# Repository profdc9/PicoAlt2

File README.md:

# Pico Alt 2

This is a simplified Pi Pico board for the new RP2350.  This has been fabricated by JLCPCB and a photograph of the result is below.  It is tested to download sketches. I customized it to add more flash (16 MB), a linear regulator (AMS1117-3.3), and to be easier to modify if needed.

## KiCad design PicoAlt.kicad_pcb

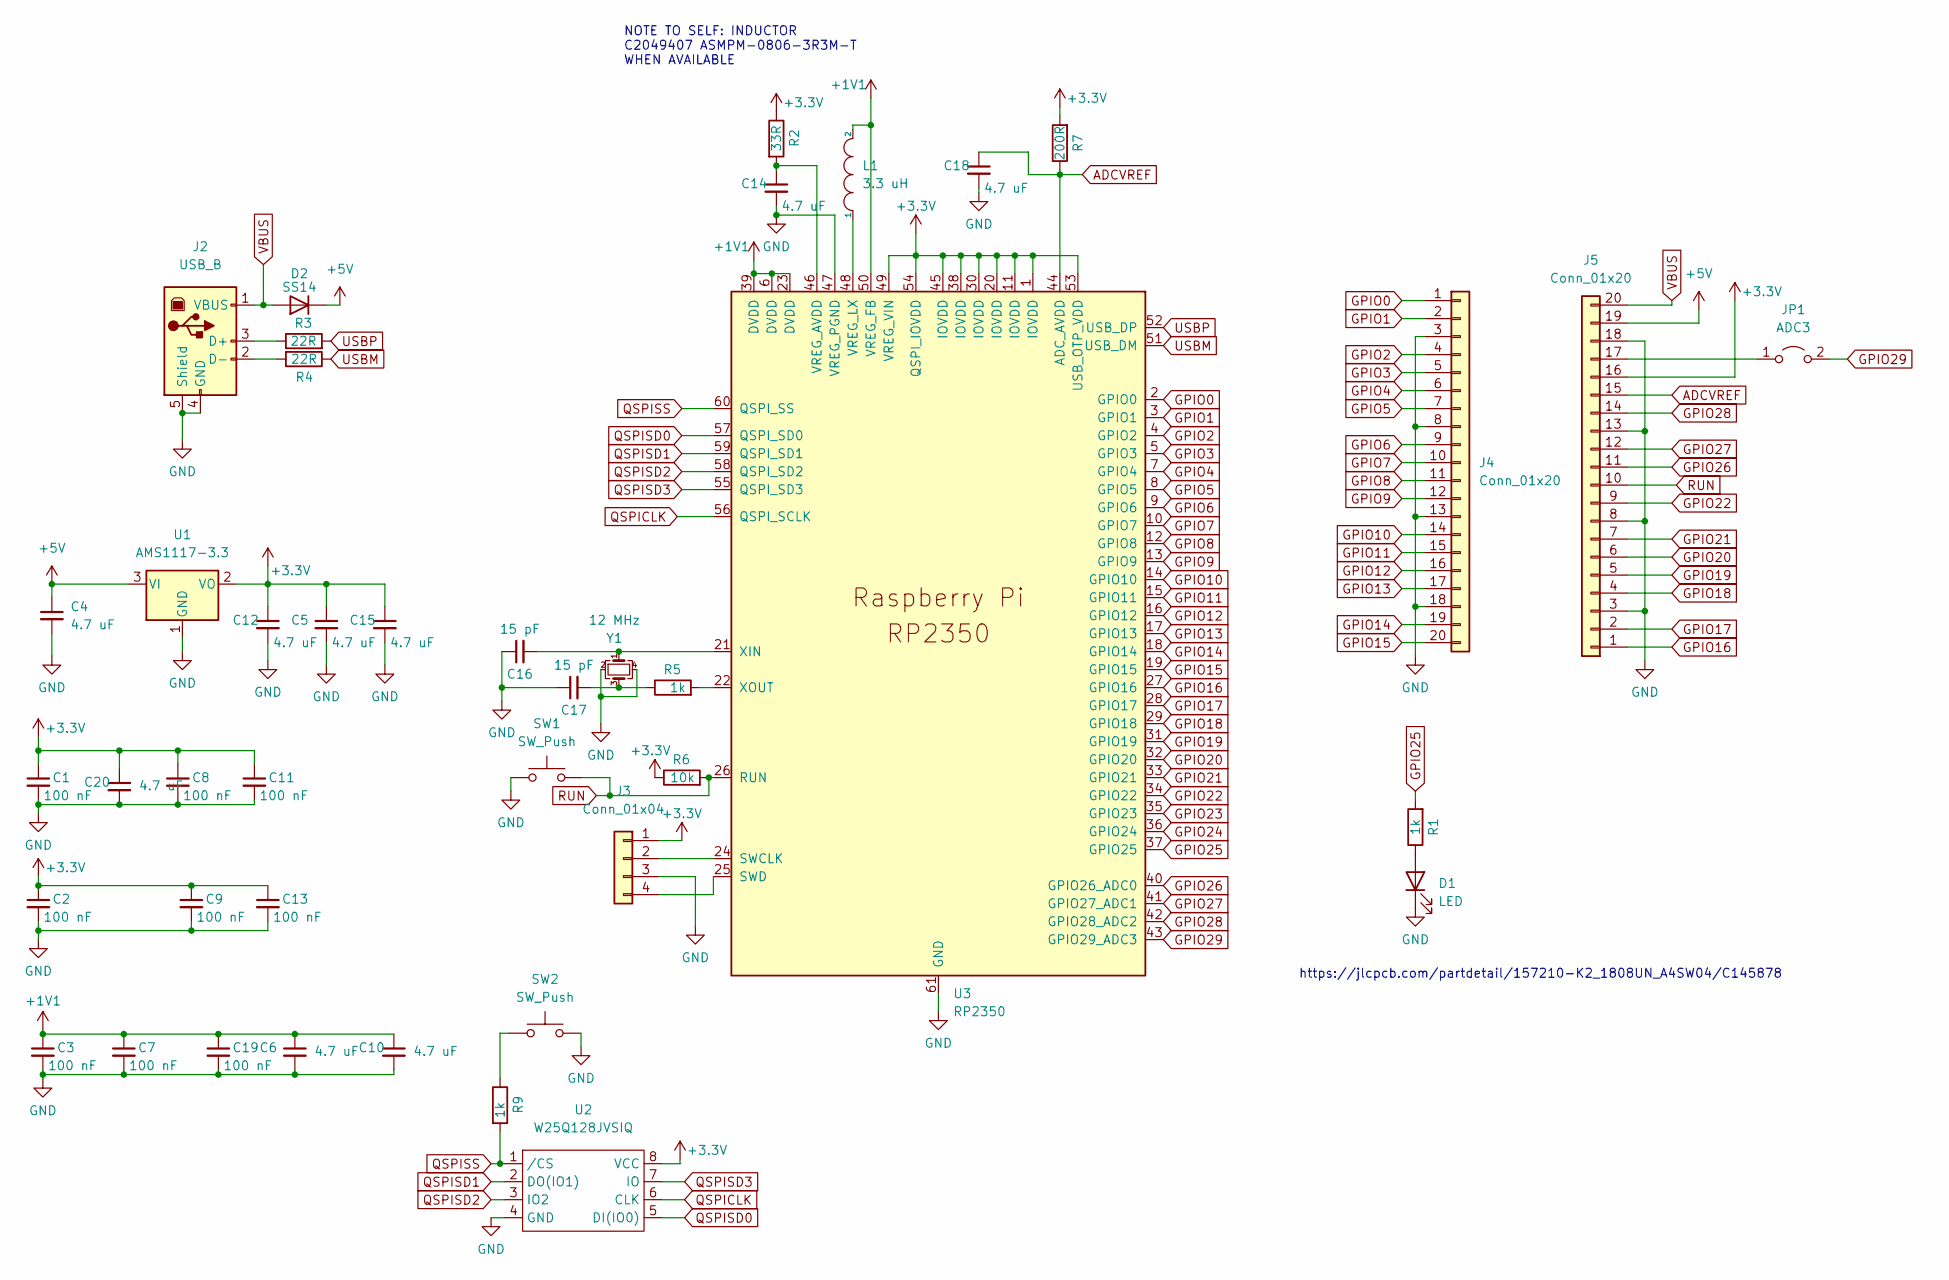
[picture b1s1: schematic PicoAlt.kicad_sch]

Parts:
C1, C2, C3, C7, C8, C9, C11, C13, C19: 100 nF; C_0402_1005Metric; LCSC C307331
C4, C5, C6, C10, C12, C14, C15, C18, C20: 4.7 uF; C_0603_1608Metric; LCSC C19666
C16, C17: 15 pF; C_0402_1005Metric; LCSC C1548
D1: LED; LED_0603_1608Metric_Pad1.05x0.95mm_HandSolder; LCSC C2286
D2: SS14; D_SMA; LCSC C2480
J2: USB_B; USB_B_OST_USB-B1HSxx_Horizontal
J3: Conn_01x04; PinHeader_1x04_P2.54mm_Vertical
J4, J5: Conn_01x20; PinHeader_1x20_P2.54mm_Vertical
JP1: ADC3; PinHeader_1x02_P2.54mm_Vertical
L1: 3.3 uH; Abracon_Pico_inductor; LCSC C42411119
R1: 1k; R_0603_1608Metric_Pad0.98x0.95mm_HandSolder; LCSC C21190
R2: 33R; R_0402_1005Metric; LCSC C25105
R3, R4: 22R; R_0402_1005Metric; LCSC C25092
R5, R9: 1k; R_0402_1005Metric; LCSC C11702
R6: 10k; R_0603_1608Metric; LCSC C25804
R7: 200R; R_0603_1608Metric_Pad0.98x0.95mm_HandSolder; LCSC C22962
SW1, SW2: SW_Push; K2-1808UN; LCSC C145878
U1: AMS1117-3.3; SOT-223-3_TabPin2; LCSC C6186
U2: W25Q128JVSIQ; SOIC-8_3.9x4.9mm_P1.27mm_mod; LCSC C97521
U3: RP2350; QFN-60-1EP_7x7mm_P0.4mm_EP3.2x3.2mm; LCSC C42411118
Y1: 12 MHz; Crystal_SMD_3225-4Pin_3.2x2.5mm; LCSC C20625731

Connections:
+1V1: C3.1, C6.1, C7.1, C10.1, C19.1, L1.2, U3.6 (DVDD), U3.23 (DVDD), U3.39 (DVDD), U3.50 (VREG_FB)
+3.3V: C1.1, C2.1, C5.1, C8.1, C9.1, C11.1, C12.1, C13.1, C15.1, C20.1, J3.1, J5.16, R2.1, R6.1, R7.2, U1.2 (VO), U2.8 (VCC), U3.1 (IOVDD), U3.11 (IOVDD), U3.20 (IOVDD), U3.30 (IOVDD), U3.38 (IOVDD), U3.45 (IOVDD), U3.49 (VREG_VIN), U3.53 (USB_OTP_VDD), U3.54 (QSPI_IOVDD)
+5V: C4.1, D2.1 (K), J5.19, U1.3 (VI)
ADCVREF: C18.1, J5.15, R7.1, U3.44 (ADC_AVDD)
GND: C1.2, C2.2, C3.2, C4.2, C5.2, C6.2, C7.2, C8.2, C9.2, C10.2, C11.2, C12.2, C13.2, C14.2, C15.2, C16.1, C17.1, C18.2, C19.2, C20.2, D1.1 (K), J2.4 (GND), J2.5 (Shield), J3.3, J4.3, J4.8, J4.13, J4.18, J5.3, J5.8, J5.13, J5.18, SW1.1, SW2.2, U1.1 (GND), U2.4 (GND), U3.47 (VREG_PGND), U3.61 (GND), Y1.2, Y1.4
GPIO0: J4.1, U3.2 (GPIO0)
GPIO1: J4.2, U3.3 (GPIO1)
GPIO2: J4.4, U3.4 (GPIO2)
GPIO3: J4.5, U3.5 (GPIO3)
GPIO4: J4.6, U3.7 (GPIO4)
GPIO5: J4.7, U3.8 (GPIO5)
GPIO6: J4.9, U3.9 (GPIO6)
GPIO7: J4.10, U3.10 (GPIO7)
GPIO8: J4.11, U3.12 (GPIO8)
GPIO9: J4.12, U3.13 (GPIO9)
GPIO10: J4.14, U3.14 (GPIO10)
GPIO11: J4.15, U3.15 (GPIO11)
GPIO12: J4.16, U3.16 (GPIO12)
GPIO13: J4.17, U3.17 (GPIO13)
GPIO14: J4.19, U3.18 (GPIO14)
GPIO15: J4.20, U3.19 (GPIO15)
GPIO16: J5.1, U3.27 (GPIO16)
GPIO17: J5.2, U3.28 (GPIO17)
GPIO18: J5.4, U3.29 (GPIO18)
GPIO19: J5.5, U3.31 (GPIO19)
GPIO20: J5.6, U3.32 (GPIO20)
GPIO21: J5.7, U3.33 (GPIO21)
GPIO22: J5.9, U3.34 (GPIO22)
GPIO23: U3.35 (GPIO23)
GPIO24: U3.36 (GPIO24)
GPIO25: R1.2, U3.37 (GPIO25)
GPIO26: J5.11, U3.40 (GPIO26_ADC0)
GPIO27: J5.12, U3.41 (GPIO27_ADC1)
GPIO28: J5.14, U3.42 (GPIO28_ADC2)
GPIO29: JP1.2 (B), U3.43 (GPIO29_ADC3)
unnamed: C17.2, R5.1, Y1.3
unnamed: D1.2 (A), R1.1
unnamed: J2.3 (D+), R3.1
unnamed: J2.2 (D-), R4.2
unnamed: J3.2, U3.24 (SWCLK)
unnamed: J3.4, U3.25 (SWD)
unnamed: J5.17, JP1.1 (A)
unnamed: R9.1, SW2.1
unnamed: C14.1, R2.2, U3.46 (VREG_AVDD)
unnamed: L1.1, U3.48 (VREG_LX)
unnamed: C16.2, U3.21 (XIN), Y1.1
unnamed: R5.2, U3.22 (XOUT)
QSPICLK: U2.6 (CLK), U3.56 (QSPI_SCLK)
QSPISD0: U2.5 (DI(IO0)), U3.57 (QSPI_SD0)
QSPISD1: U2.2 (DO(IO1)), U3.59 (QSPI_SD1)
QSPISD2: U2.3 (IO2), U3.58 (QSPI_SD2)
QSPISD3: U2.7 (IO), U3.55 (QSPI_SD3)
QSPISS: R9.2, U2.1 (/CS), U3.60 (QSPI_SS)
RUN: J5.10, R6.2, SW1.2, U3.26 (RUN)
USBM: R4.1, U3.51 (USB_DM)
USBP: R3.2, U3.52 (USB_DP)
VBUS: D2.2 (A), J2.1 (VBUS), J5.20

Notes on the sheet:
https://jlcpcb.com/partdetail/157210-K2_1808UN_A4SW04/C145878
NOTE TO SELF: INDUCTOR C2049407 ASMPM-0806-3R3M-T WHEN AVAILABLE

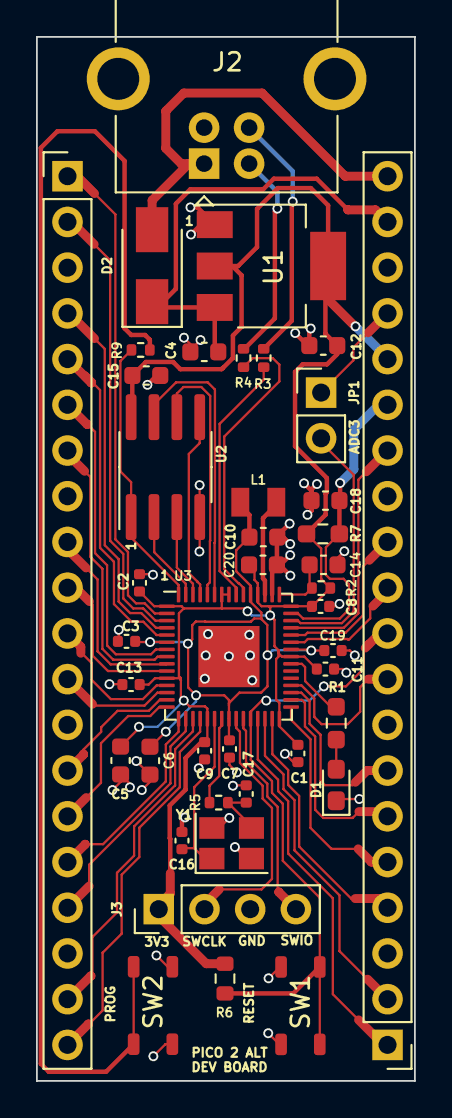
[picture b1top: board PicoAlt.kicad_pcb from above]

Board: 2 copper layers, 21.0 x 58.0 mm, 42 parts (0 on the bottom side), 55 nets.

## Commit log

2024-08-10 rearranged layout
2024-08-11 Small modifications of placement
2024-08-12 regulator work
2024-08-13 Changed inductor
2025-09-06 Modified for Abracon inductor and oscillator, sent to JLCPCB
2025-09-16 Added photo
